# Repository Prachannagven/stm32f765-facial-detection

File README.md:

# Introduction
The goal of this project is to build a 50x50mm drone, capable of autonomous flight, and recognizing humans. The final product should be able to fly towards the target.

For current protyping, I'm looking at using an OV7670 camera, which supplies up to a 320x260 frame, based on the qvga output. However, I can go as low as the qcif resolution (176x144), although I'm not sure recognition will work well on that.

# Links to Look at
[OV7670 Interfacing][https://www.youtube.com/watch?v=aanNau1RDTA]

# Hardware Design
I use an STM32F765VIT6 due to its on board DCMI block, as well as its ART accelerator to speed up computations. It pairs with a TOF sensor, a BMP280 barometer, IMU and magnetic field sensor for full attitude determination.

Four brushed DC motors are used for this system, allowing for lightweight control. The only limitation here is how heavy the entire system is going to be. It can carry approximately 100-200 grams, which is well within our weight budget.

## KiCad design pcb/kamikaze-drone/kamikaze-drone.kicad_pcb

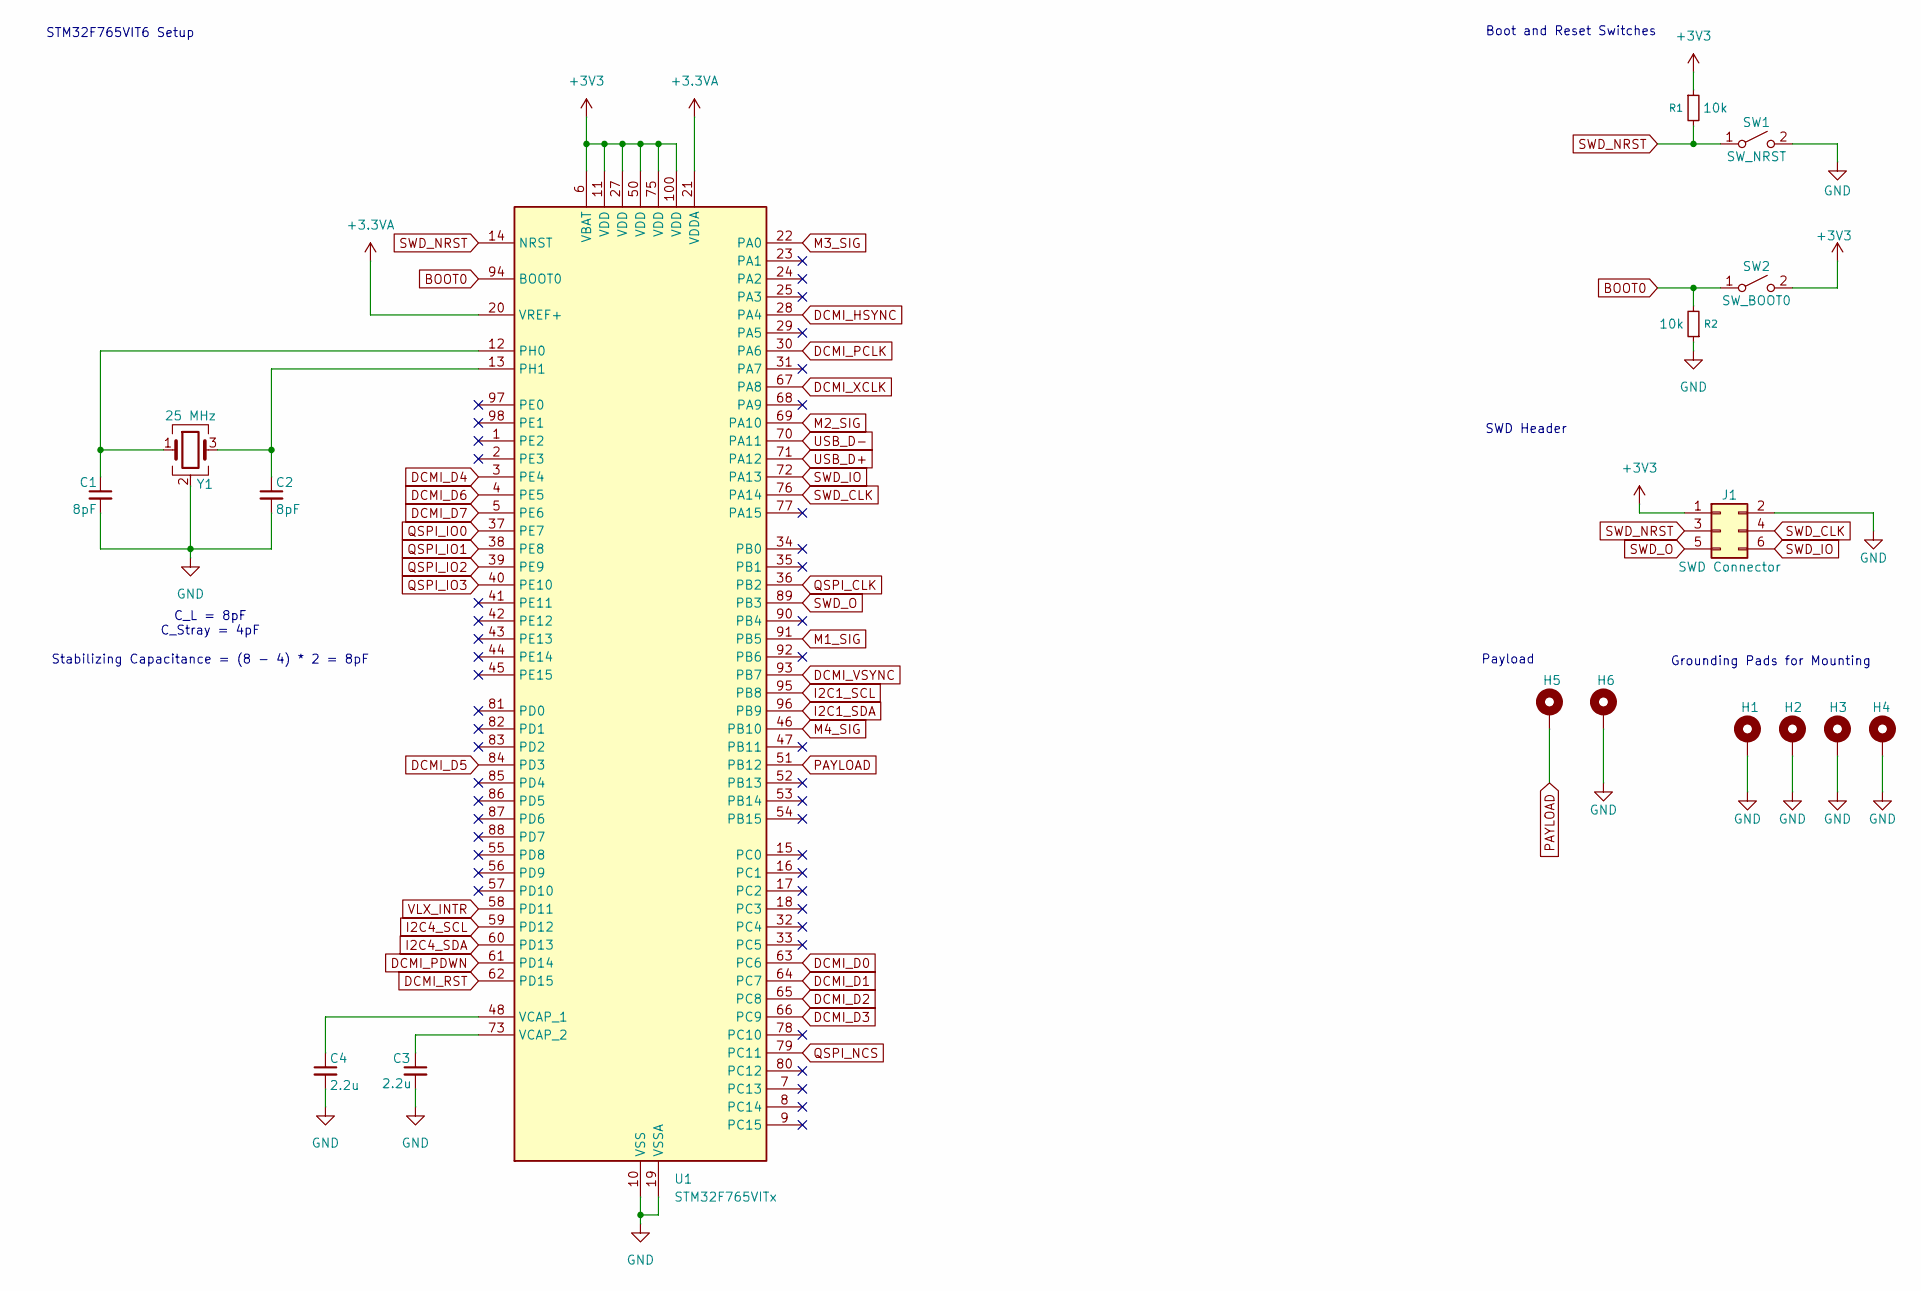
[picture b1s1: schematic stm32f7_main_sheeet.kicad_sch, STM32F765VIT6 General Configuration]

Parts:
C1, C2: 8pF; C_0603_1608Metric_Pad1.08x0.95mm_HandSolder
C3, C4: 2.2u; C_0805_2012Metric_Pad1.18x1.45mm_HandSolder
H1, H2, H3, H4: Gnd; MountingHole_2.2mm_M2_DIN965_Pad_TopBottom
H5, H6: Gnd; payload-pad
J1: SWD Connector; PinHeader_2x03_P2.54mm_Vertical_SMD
R1, R2: 10k; R_0603_1608Metric_Pad0.98x0.95mm_HandSolder
SW1: SW_NRST; button-footprint
SW2: SW_BOOT0; SW_DIP_SPSTx01_Slide_6.7x4.1mm_W6.73mm_P2.54mm_LowProfile_J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
U1: STM32F765VITx; LQFP-100_14x14mm_P0.5mm
Y1: 25 MHz; crysal-25MHz-2.55mm_x_2.05mm-2-4G

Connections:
+3.3VA: U1.20 (VREF+), U1.21 (VDDA); also elsewhere on the board
+3V3: J1.1, R1.1, SW2.2 (B), U1.6 (VBAT), U1.11 (VDD), U1.27 (VDD), U1.50 (VDD), U1.75 (VDD), U1.100 (VDD); also elsewhere on the board
BOOT0: R2.2, SW2.1 (A), U1.94 (BOOT0)
DCMI_D0: U1.63 (PC6); also elsewhere on the board
DCMI_D1: U1.64 (PC7); also elsewhere on the board
DCMI_D2: U1.65 (PC8); also elsewhere on the board
DCMI_D3: U1.66 (PC9); also elsewhere on the board
DCMI_D4: U1.3 (PE4); also elsewhere on the board
DCMI_D5: U1.84 (PD3); also elsewhere on the board
DCMI_D6: U1.4 (PE5); also elsewhere on the board
DCMI_D7: U1.5 (PE6); also elsewhere on the board
DCMI_HSYNC: U1.28 (PA4); also elsewhere on the board
DCMI_PCLK: U1.30 (PA6); also elsewhere on the board
DCMI_PDWN: U1.61 (PD14); also elsewhere on the board
DCMI_RST: U1.62 (PD15); also elsewhere on the board
DCMI_VSYNC: U1.93 (PB7); also elsewhere on the board
DCMI_XCLK: U1.67 (PA8); also elsewhere on the board
GND: C1.2, C2.2, C3.2, C4.2, H1.1, H2.1, H3.1, H4.1, H6.1, J1.2, R2.1, SW1.2 (B), U1.10 (VSS), U1.19 (VSSA), U1.26 (VSS), U1.49 (VSS), U1.74 (VSS), U1.99 (VSS), Y1.2 (G), Y1.4 (G); also elsewhere on the board
I2C1_SCL: U1.95 (PB8); also elsewhere on the board
I2C1_SDA: U1.96 (PB9); also elsewhere on the board
I2C4_SCL: U1.59 (PD12); also elsewhere on the board
I2C4_SDA: U1.60 (PD13); also elsewhere on the board
M1_SIG: U1.91 (PB5); also elsewhere on the board
M2_SIG: U1.69 (PA10); also elsewhere on the board
M3_SIG: U1.22 (PA0); also elsewhere on the board
M4_SIG: U1.46 (PB10); also elsewhere on the board
unnamed: C1.1, U1.12 (PH0), Y1.1
unnamed: C2.1, U1.13 (PH1), Y1.3
unnamed: C4.1, U1.48 (VCAP_1)
unnamed: C3.1, U1.73 (VCAP_2)
PAYLOAD: H5.1, U1.51 (PB12)
QSPI_CLK: U1.36 (PB2); also elsewhere on the board
QSPI_IO0: U1.37 (PE7); also elsewhere on the board
QSPI_IO1: U1.38 (PE8); also elsewhere on the board
QSPI_IO2: U1.39 (PE9); also elsewhere on the board
QSPI_IO3: U1.40 (PE10); also elsewhere on the board
QSPI_NCS: U1.79 (PC11); also elsewhere on the board
SWD_CLK: J1.4, U1.76 (PA14)
SWD_IO: J1.6, U1.72 (PA13)
SWD_NRST: J1.3, R1.2, SW1.1 (A), U1.14 (NRST)
SWD_O: J1.5, U1.89 (PB3)
USB_D+: U1.71 (PA12); also elsewhere on the board
USB_D-: U1.70 (PA11); also elsewhere on the board
VLX_INTR: U1.58 (PD11); also elsewhere on the board

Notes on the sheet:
Payload
Grounding Pads for Mounting
C_L = 8pF C_Stray = 4pF Stabilizing Capacitance = (8 - 4) * 2 = 8pF
Boot and Reset Switches
SWD Header
STM32F765VIT6 Setup

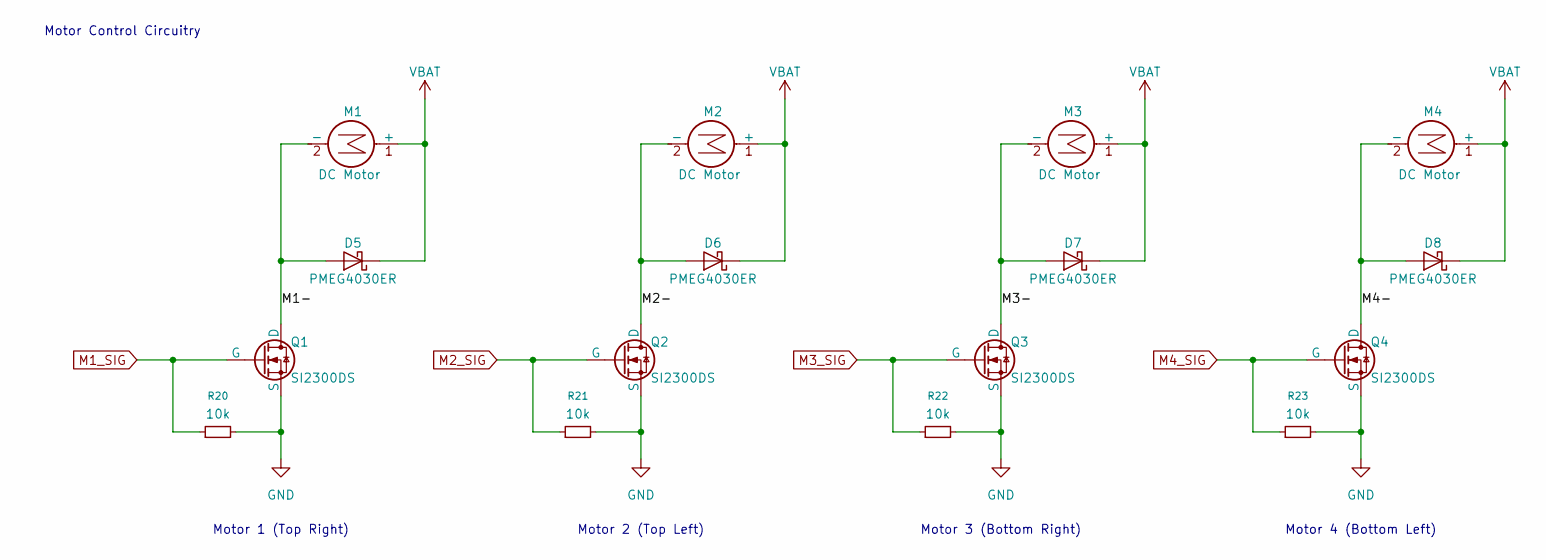
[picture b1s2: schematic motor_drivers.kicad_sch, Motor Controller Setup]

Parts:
D5, D6, D7, D8: PMEG4030ER; Nexperia_CFP3_SOD-123W
M1, M2, M3, M4: DC Motor; motor-attachment-pads
Q1, Q2, Q3, Q4: SI2300DS; SOT-23-3
R20, R21, R22, R23: 10k; R_0603_1608Metric_Pad0.98x0.95mm_HandSolder

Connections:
/Motors and Motor Drivers/M1-: D5.2 (A), M1.2 (-), Q1.3 (D)
/Motors and Motor Drivers/M2-: D6.2 (A), M2.2 (-), Q2.3 (D)
/Motors and Motor Drivers/M3-: D7.2 (A), M3.2 (-), Q3.3 (D)
/Motors and Motor Drivers/M4-: D8.2 (A), M4.2 (-), Q4.3 (D)
GND: Q1.2 (S), Q2.2 (S), Q3.2 (S), Q4.2 (S), R20.2, R21.2, R22.2, R23.2; also elsewhere on the board
M1_SIG: Q1.1 (G), R20.1; also elsewhere on the board
M2_SIG: Q2.1 (G), R21.1; also elsewhere on the board
M3_SIG: Q3.1 (G), R22.1; also elsewhere on the board
M4_SIG: Q4.1 (G), R23.1; also elsewhere on the board
VBAT: D5.1 (K), D6.1 (K), D7.1 (K), D8.1 (K), M1.1 (+), M2.1 (+), M3.1 (+), M4.1 (+); also elsewhere on the board

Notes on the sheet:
Motor 4 (Bottom Left)
Motor Control Circuitry
Motor 2 (Top Left)
Motor 1 (Top Right)
Motor 3 (Bottom Right)

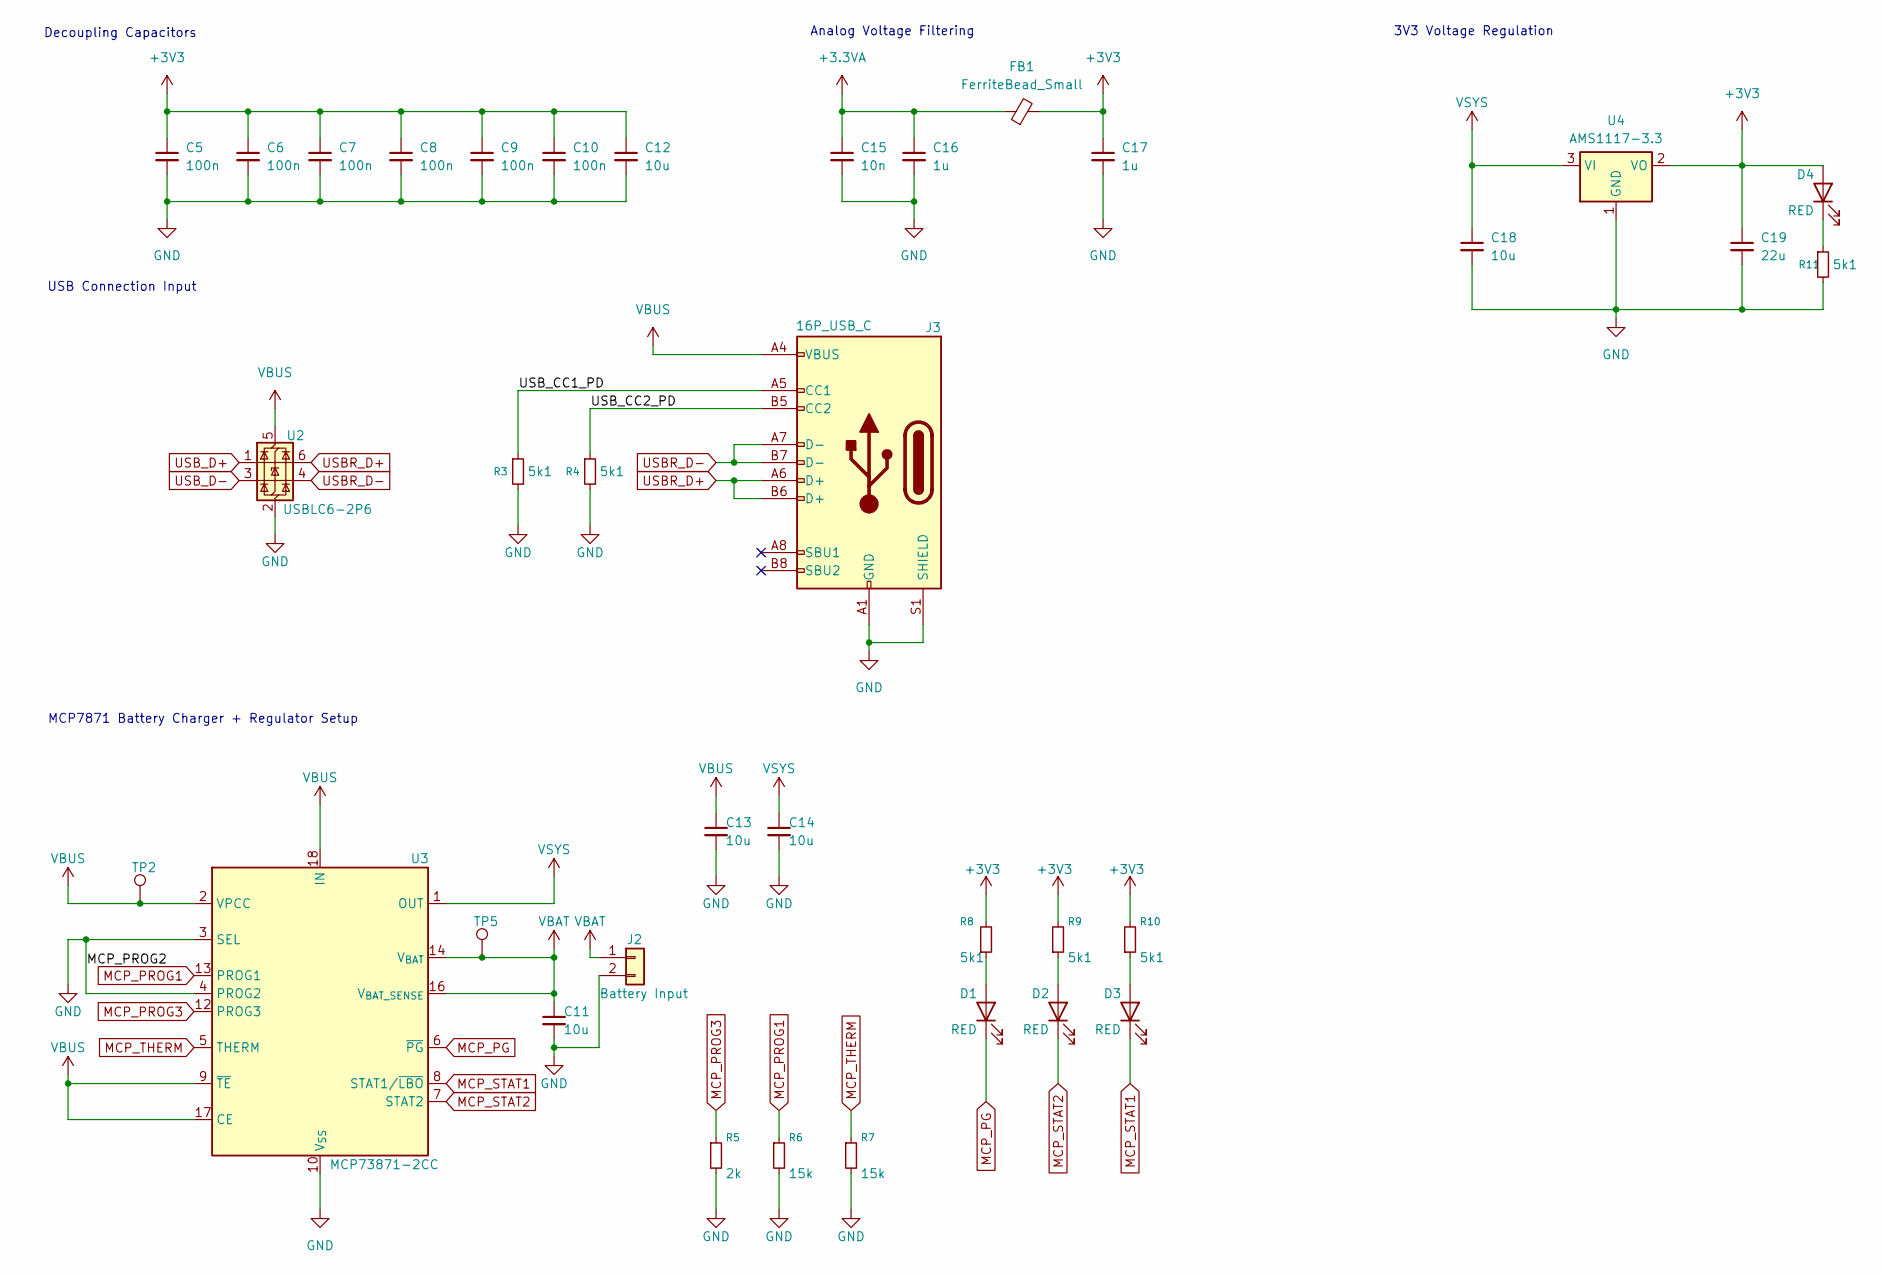
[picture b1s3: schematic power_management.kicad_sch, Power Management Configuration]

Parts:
C5, C6, C7, C8, C9, C10: 100n; C_0603_1608Metric_Pad1.08x0.95mm_HandSolder
C11, C13, C14, C18: 10u; C_0603_1608Metric_Pad1.08x0.95mm_HandSolder
C12: 10u; C_0805_2012Metric_Pad1.18x1.45mm_HandSolder
C15: 10n; C_0603_1608Metric_Pad1.08x0.95mm_HandSolder
C16, C17: 1u; C_0603_1608Metric_Pad1.08x0.95mm_HandSolder
C19: 22u; C_0603_1608Metric_Pad1.08x0.95mm_HandSolder
D1, D2, D3, D4: RED; LED_0805_2012Metric_Pad1.15x1.40mm_HandSolder
FB1: FerriteBead_Small; L_0805_2012Metric_Pad1.05x1.20mm_HandSolder
J2: Battery Input; motor-attachment-pads
J3: 16P_USB_C; USB_C_Receptacle_G-Switch_GT-USB-7010ASV
R3, R4, R8, R9, R10, R11: 5k1; R_0603_1608Metric_Pad0.98x0.95mm_HandSolder
R5: 2k; R_0603_1608Metric_Pad0.98x0.95mm_HandSolder
R6, R7: 15k; R_0603_1608Metric_Pad0.98x0.95mm_HandSolder
TP2, TP5: TestPoint; TestPoint_Pad_D1.0mm
U2: USBLC6-2P6; SOT-666
U3: MCP73871-2CC; QFN-20-1EP_4x4mm_P0.5mm_EP2.5x2.5mm
U4: AMS1117-3.3; SOT-223-3_TabPin2

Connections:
+3.3VA: C15.1, C16.1, FB1.1; also elsewhere on the board
+3V3: C5.1, C6.1, C7.1, C8.1, C9.1, C10.1, C12.1, C17.1, C19.1, D4.2 (A), FB1.2, R8.2, R9.2, R10.2, U4.2 (VO); also elsewhere on the board
/Power Management/USB_CC1_PD: J3.A5 (CC1), R3.1
/Power Management/USB_CC2_PD: J3.B5 (CC2), R4.1
GND: C5.2, C6.2, C7.2, C8.2, C9.2, C10.2, C11.2, C12.2, C13.2, C14.2, C15.2, C16.2, C17.2, C18.2, C19.2, J2.2, J3.A1 (GND), J3.A12 (GND), J3.B1 (GND), J3.B12 (GND), J3.S1 (SHIELD), R3.2, R4.2, R5.2, R6.2, R7.2, R11.2, U2.2 (GND), U3.3 (SEL), U3.4 (PROG2), U3.10 (V_{SS}), U3.11 (V_{SS}), U3.21 (V_{SS}), U4.1 (GND); also elsewhere on the board
MCP_PG: D1.1 (K), U3.6 (~PG)
MCP_PROG1: R6.1, U3.13 (PROG1)
MCP_PROG3: R5.1, U3.12 (PROG3)
MCP_STAT1: D3.1 (K), U3.8 (STAT1/~LBO)
MCP_STAT2: D2.1 (K), U3.7 (STAT2)
MCP_THERM: R7.1, U3.5 (THERM)
unnamed: D1.2 (A), R8.1
unnamed: D2.2 (A), R9.1
unnamed: D3.2 (A), R10.1
unnamed: D4.1 (K), R11.1
USBR_D+: J3.A6 (D+), J3.B6 (D+), U2.6 (I/O1)
USBR_D-: J3.A7 (D-), J3.B7 (D-), U2.4 (I/O2)
USB_D+: U2.1 (I/O1); also elsewhere on the board
USB_D-: U2.3 (I/O2); also elsewhere on the board
VBAT: C11.1, J2.1, TP5.1, U3.14 (V_{BAT}), U3.15 (V_{BAT}), U3.16 (V_{BAT_SENSE}); also elsewhere on the board
VBUS: C13.1, J3.A4 (VBUS), J3.A9 (VBUS), J3.B4 (VBUS), J3.B9 (VBUS), TP2.1, U2.5 (VBUS), U3.2 (VPCC), U3.9 (~TE), U3.17 (CE), U3.18 (IN), U3.19 (IN)
VSYS: C14.1, C18.1, U3.1 (OUT), U3.20 (OUT), U4.3 (VI)

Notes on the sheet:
MCP7871 Battery Charger + Regulator Setup
Analog Voltage Filtering
3V3 Voltage Regulation
USB Connection Input
Decoupling Capacitors

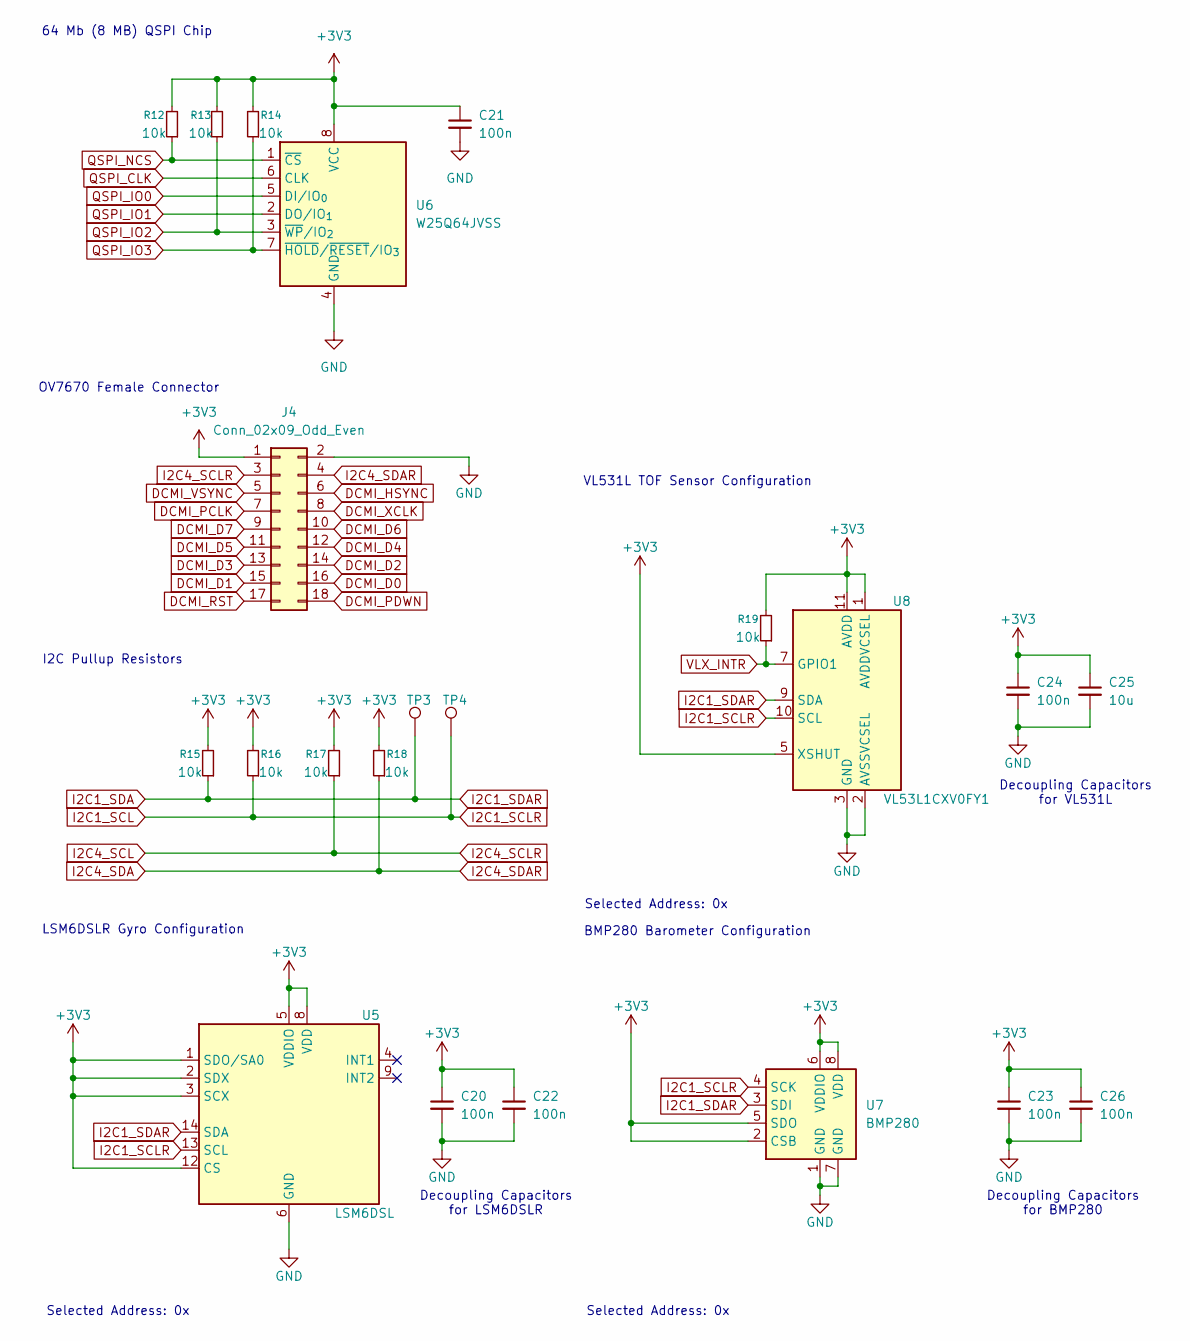
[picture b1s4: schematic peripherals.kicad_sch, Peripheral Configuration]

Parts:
C20, C21, C22, C23, C24, C26: 100n; C_0603_1608Metric_Pad1.08x0.95mm_HandSolder
C25: 10u; C_0603_1608Metric_Pad1.08x0.95mm_HandSolder
J4: Conn_02x09_Odd_Even; IDC-Header_2x09_P2.54mm_Horizontal
R12, R13, R14, R15, R16, R17, R18, R19: 10k; R_0603_1608Metric_Pad0.98x0.95mm_HandSolder
TP3, TP4: TestPoint; TestPoint_Pad_D1.0mm
U5: LSM6DSL; LGA-14_3x2.5mm_P0.5mm_LayoutBorder3x4y
U6: W25Q64JVSS; SOIC-8_5.3x5.3mm_P1.27mm
U7: BMP280; Bosch_LGA-8_2x2.5mm_P0.65mm_ClockwisePinNumbering
U8: VL53L1CXV0FY1; ST_VL53L1x

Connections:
+3V3: C20.1, C21.1, C22.1, C23.1, C24.1, C25.1, C26.1, J4.1, R12.2, R13.2, R14.2, R15.2, R16.2, R17.2, R18.2, R19.2, U5.1 (SDO/SA0), U5.2 (SDX), U5.3 (SCX), U5.5 (VDDIO), U5.8 (VDD), U5.12 (CS), U6.8 (VCC), U7.2 (CSB), U7.5 (SDO), U7.6 (VDDIO), U7.8 (VDD), U8.1 (AVDDVCSEL), U8.5 (XSHUT), U8.11 (AVDD); also elsewhere on the board
DCMI_D0: J4.16; also elsewhere on the board
DCMI_D1: J4.15; also elsewhere on the board
DCMI_D2: J4.14; also elsewhere on the board
DCMI_D3: J4.13; also elsewhere on the board
DCMI_D4: J4.12; also elsewhere on the board
DCMI_D5: J4.11; also elsewhere on the board
DCMI_D6: J4.10; also elsewhere on the board
DCMI_D7: J4.9; also elsewhere on the board
DCMI_HSYNC: J4.6; also elsewhere on the board
DCMI_PCLK: J4.7; also elsewhere on the board
DCMI_PDWN: J4.18; also elsewhere on the board
DCMI_RST: J4.17; also elsewhere on the board
DCMI_VSYNC: J4.5; also elsewhere on the board
DCMI_XCLK: J4.8; also elsewhere on the board
GND: C20.2, C21.2, C22.2, C23.2, C24.2, C25.2, C26.2, J4.2, U5.6 (GND), U5.7 (GND), U6.4 (GND), U7.1 (GND), U7.7 (GND), U8.2 (AVSSVCSEL), U8.3 (GND), U8.4 (GND), U8.6 (GND), U8.12 (GND); also elsewhere on the board
I2C1_SCL: R16.1, TP4.1, U5.13 (SCL), U7.4 (SCK), U8.10 (SCL); also elsewhere on the board
I2C1_SDA: R15.1, TP3.1, U5.14 (SDA), U7.3 (SDI), U8.9 (SDA); also elsewhere on the board
I2C4_SCL: J4.3, R17.1; also elsewhere on the board
I2C4_SDA: J4.4, R18.1; also elsewhere on the board
QSPI_CLK: U6.6 (CLK); also elsewhere on the board
QSPI_IO0: U6.5 (DI/IO_{0}); also elsewhere on the board
QSPI_IO1: U6.2 (DO/IO_{1}); also elsewhere on the board
QSPI_IO2: R13.1, U6.3 (~WP/IO_{2}); also elsewhere on the board
QSPI_IO3: R14.1, U6.7 (~HOLD/~RESET/IO_{3}); also elsewhere on the board
QSPI_NCS: R12.1, U6.1 (~CS); also elsewhere on the board
VLX_INTR: R19.1, U8.7 (GPIO1); also elsewhere on the board

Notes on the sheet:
I2C Pullup Resistors
Decoupling Capacitors for VL531L
64 Mb (8 MB) QSPI Chip
LSM6DSLR Gyro Configuration
Selected Address: 0x
Decoupling Capacitors for BMP280
VL531L TOF Sensor Configuration
Decoupling Capacitors for LSM6DSLR
BMP280 Barometer Configuration
OV7670 Female Connector

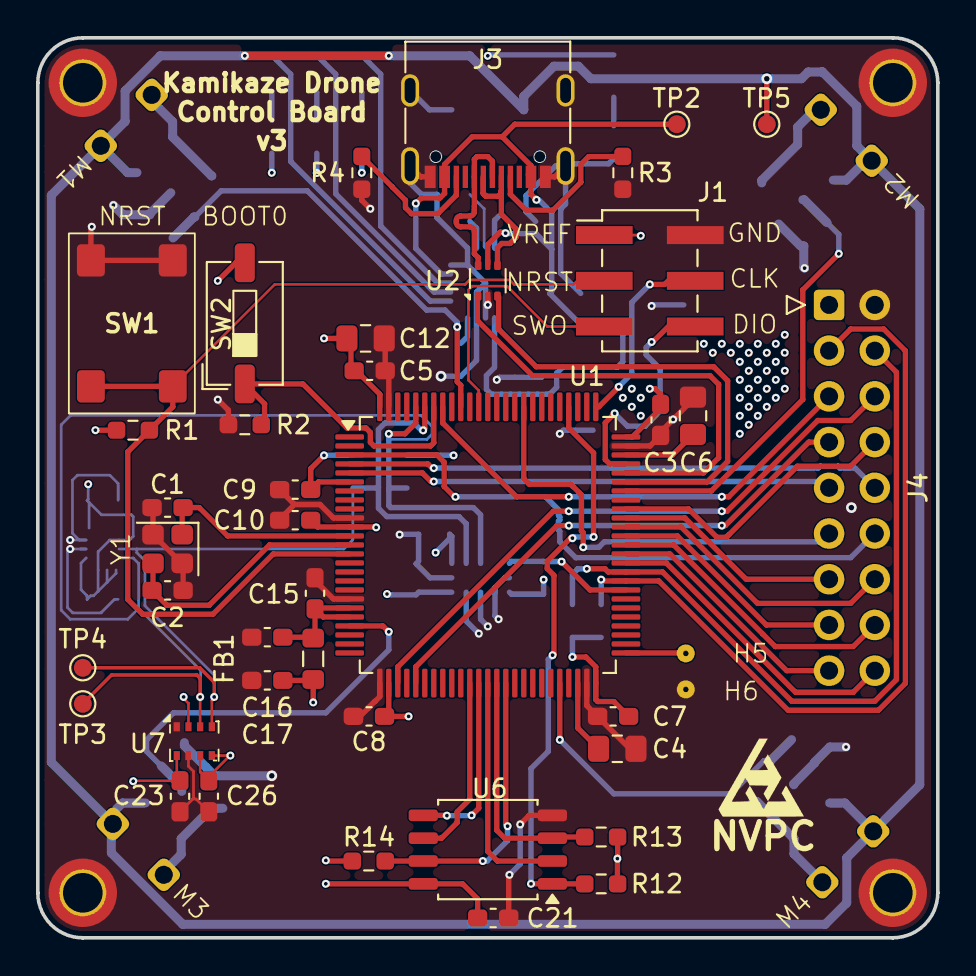
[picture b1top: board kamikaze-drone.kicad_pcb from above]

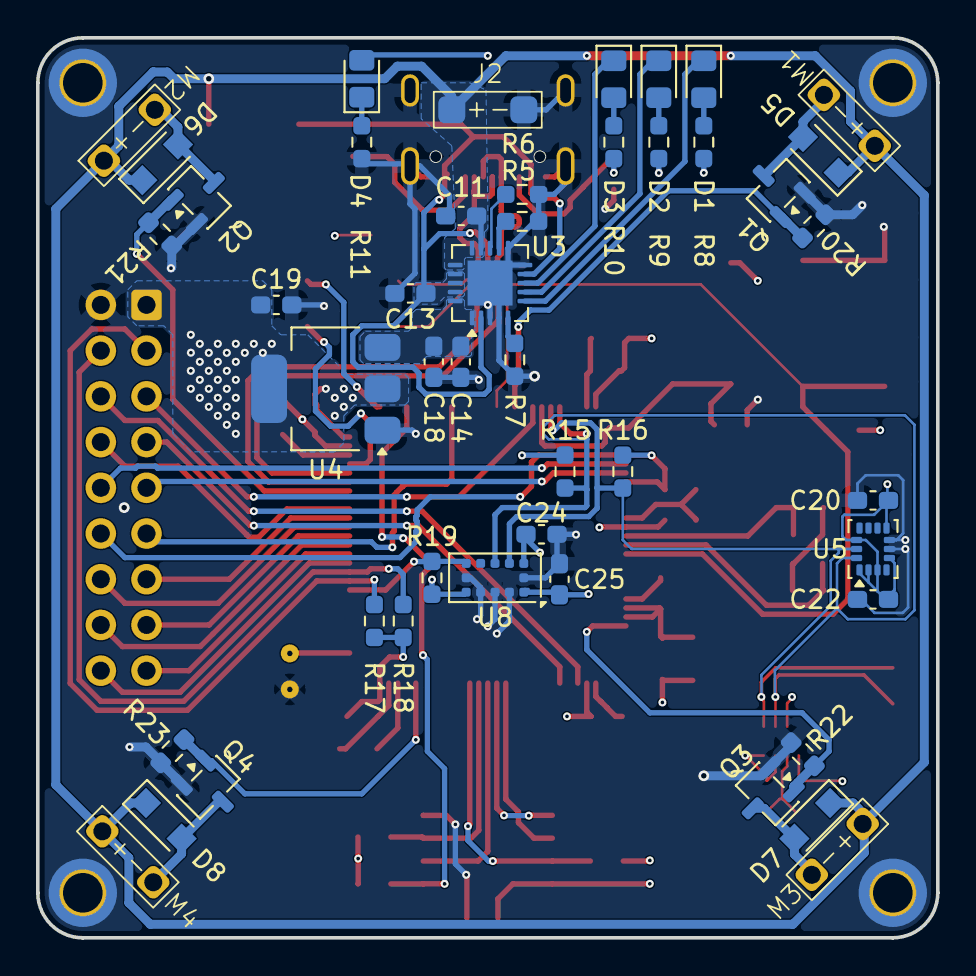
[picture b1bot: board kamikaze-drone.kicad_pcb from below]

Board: 4 copper layers, 50.0 x 50.0 mm, 92 parts (46 on the bottom side), 65 nets.

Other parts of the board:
NVPC: LOGO; logo

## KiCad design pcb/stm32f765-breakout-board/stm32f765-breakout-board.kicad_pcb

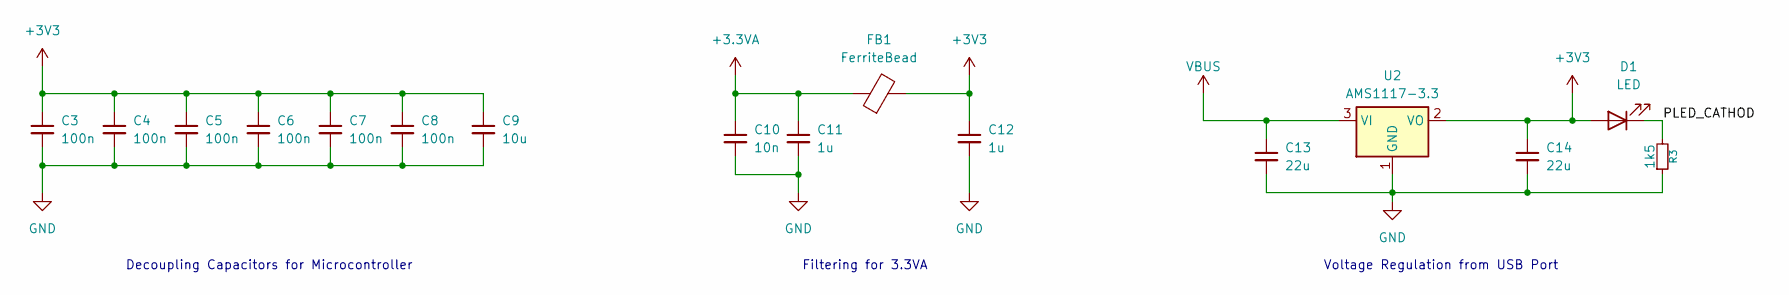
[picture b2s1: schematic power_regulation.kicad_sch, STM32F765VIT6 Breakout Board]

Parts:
C3, C4, C5, C6, C7, C8: 100n; C_0805_2012Metric_Pad1.18x1.45mm_HandSolder
C9: 10u; C_0805_2012Metric_Pad1.18x1.45mm_HandSolder
C10: 10n; C_0805_2012Metric_Pad1.18x1.45mm_HandSolder
C11, C12: 1u; C_0805_2012Metric_Pad1.18x1.45mm_HandSolder
C13, C14: 22u; C_0805_2012Metric_Pad1.18x1.45mm_HandSolder
D1: LED; LED_0805_2012Metric_Pad1.15x1.40mm_HandSolder
FB1: FerriteBead; L_0805_2012Metric_Pad1.05x1.20mm_HandSolder
R3: 1k5; R_0805_2012Metric_Pad1.20x1.40mm_HandSolder
U2: AMS1117-3.3; SOT-223-3_TabPin2

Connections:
+3.3VA: C10.1, C11.1, FB1.1; also elsewhere on the board
+3V3: C3.1, C4.1, C5.1, C6.1, C7.1, C8.1, C9.1, C12.1, C14.1, D1.2 (A), FB1.2, U2.2 (VO); also elsewhere on the board
/Power Regulation/PLED_CATHOD: D1.1 (K), R3.2
GND: C3.2, C4.2, C5.2, C6.2, C7.2, C8.2, C9.2, C10.2, C11.2, C12.2, C13.2, C14.2, R3.1, U2.1 (GND); also elsewhere on the board
VBUS: C13.1, U2.3 (VI); also elsewhere on the board

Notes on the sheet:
Filtering for 3.3VA
Voltage Regulation from USB Port
Decoupling Capacitors for Microcontroller

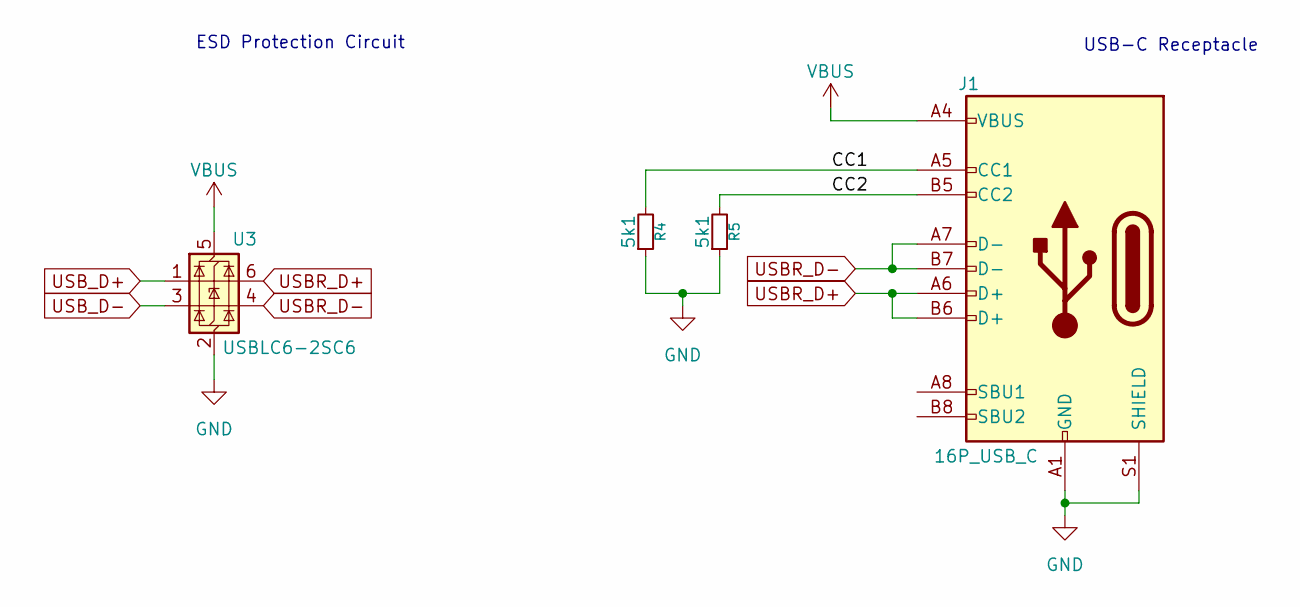
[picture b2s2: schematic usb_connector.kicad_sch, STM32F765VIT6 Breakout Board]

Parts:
J1: 16P_USB_C; USB_C_Receptacle_G-Switch_GT-USB-7010ASV
R4, R5: 5k1; R_0805_2012Metric_Pad1.20x1.40mm_HandSolder
U3: USBLC6-2SC6; SOT-23-6

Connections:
/USB Connector/CC1: J1.A5 (CC1), R4.2
/USB Connector/CC2: J1.B5 (CC2), R5.2
GND: J1.A1 (GND), J1.A12 (GND), J1.B1 (GND), J1.B12 (GND), J1.S1 (SHIELD), R4.1, R5.1, U3.2 (GND); also elsewhere on the board
USBR_D+: J1.A6 (D+), J1.B6 (D+), U3.6 (I/O1)
USBR_D-: J1.A7 (D-), J1.B7 (D-), U3.4 (I/O2)
USB_D+: U3.1 (I/O1); also elsewhere on the board
USB_D-: U3.3 (I/O2); also elsewhere on the board
VBUS: J1.A4 (VBUS), J1.A9 (VBUS), J1.B4 (VBUS), J1.B9 (VBUS), U3.5 (VBUS); also elsewhere on the board

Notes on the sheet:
USB-C Receptacle
ESD Protection Circuit

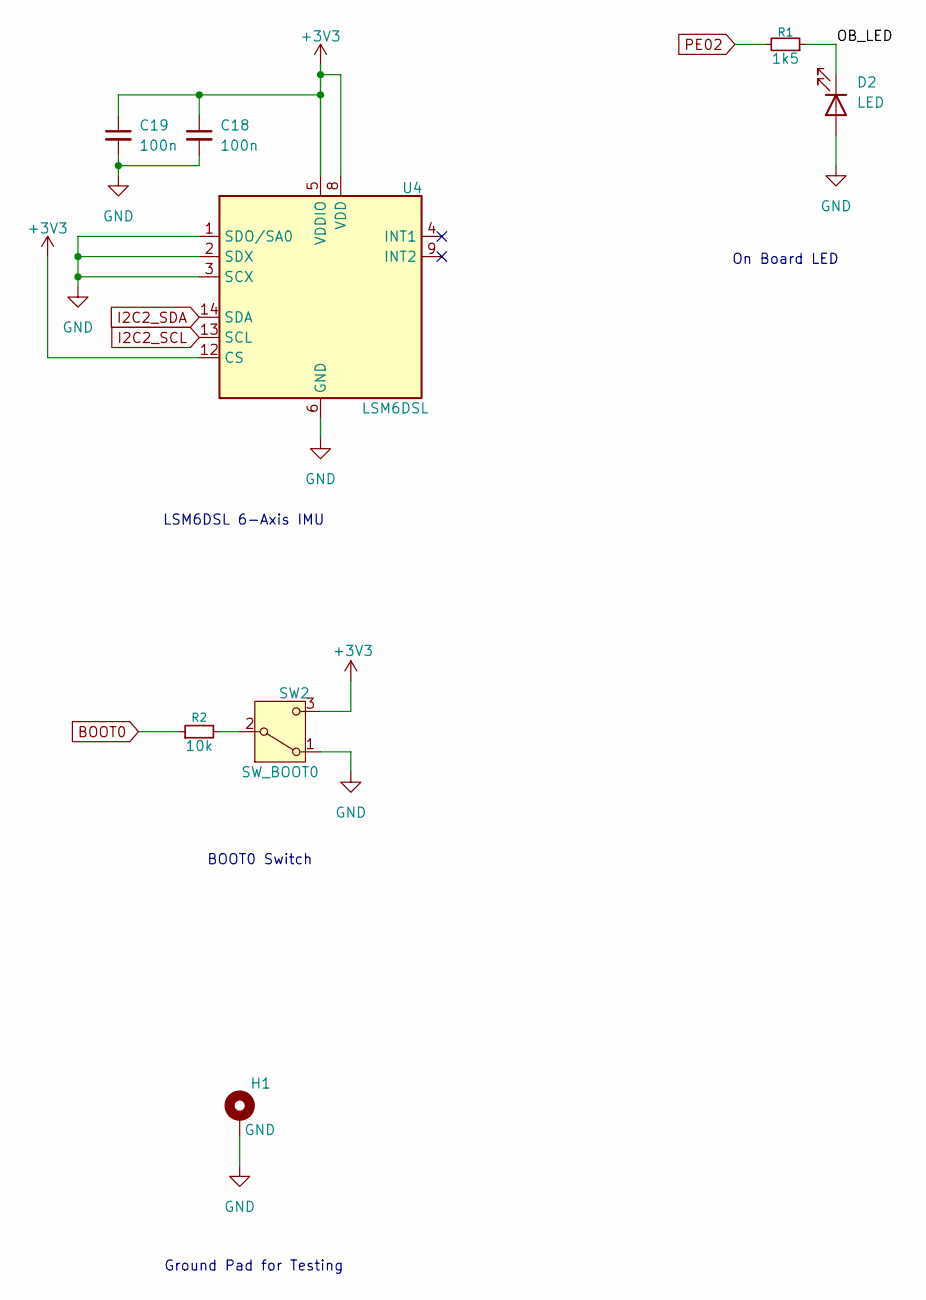
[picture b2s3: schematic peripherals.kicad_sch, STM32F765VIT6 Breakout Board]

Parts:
C18, C19: 100n; C_0805_2012Metric_Pad1.18x1.45mm_HandSolder
D2: LED; LED_0805_2012Metric_Pad1.15x1.40mm_HandSolder
H1: GND; MountingHole_2.2mm_M2_Pad
R1: 1k5; R_0805_2012Metric_Pad1.20x1.40mm_HandSolder
R2: 10k; R_0805_2012Metric_Pad1.20x1.40mm_HandSolder
SW2: SW_BOOT0; new_4.5x4.5_mm_tactile_button_1883759
U4: LSM6DSL; LGA-14_3x2.5mm_P0.5mm_LayoutBorder3x4y

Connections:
+3V3: C18.1, C19.1, SW2.3 (C), U4.5 (VDDIO), U4.8 (VDD), U4.12 (CS); also elsewhere on the board
/Peripherals/OB_LED: D2.1 (K), R1.1
BOOT0: R2.1; also elsewhere on the board
GND: C18.2, C19.2, D2.2 (A), H1.1, SW2.1 (A), U4.1 (SDO/SA0), U4.2 (SDX), U4.3 (SCX), U4.6 (GND), U4.7 (GND); also elsewhere on the board
I2C2_SCL: U4.13 (SCL); also elsewhere on the board
I2C2_SDA: U4.14 (SDA); also elsewhere on the board
unnamed: R2.2, SW2.2 (B)
PE02: R1.2; also elsewhere on the board

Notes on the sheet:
LSM6DSL 6-Axis IMU
Ground Pad for Testing
On Board LED
BOOT0 Switch

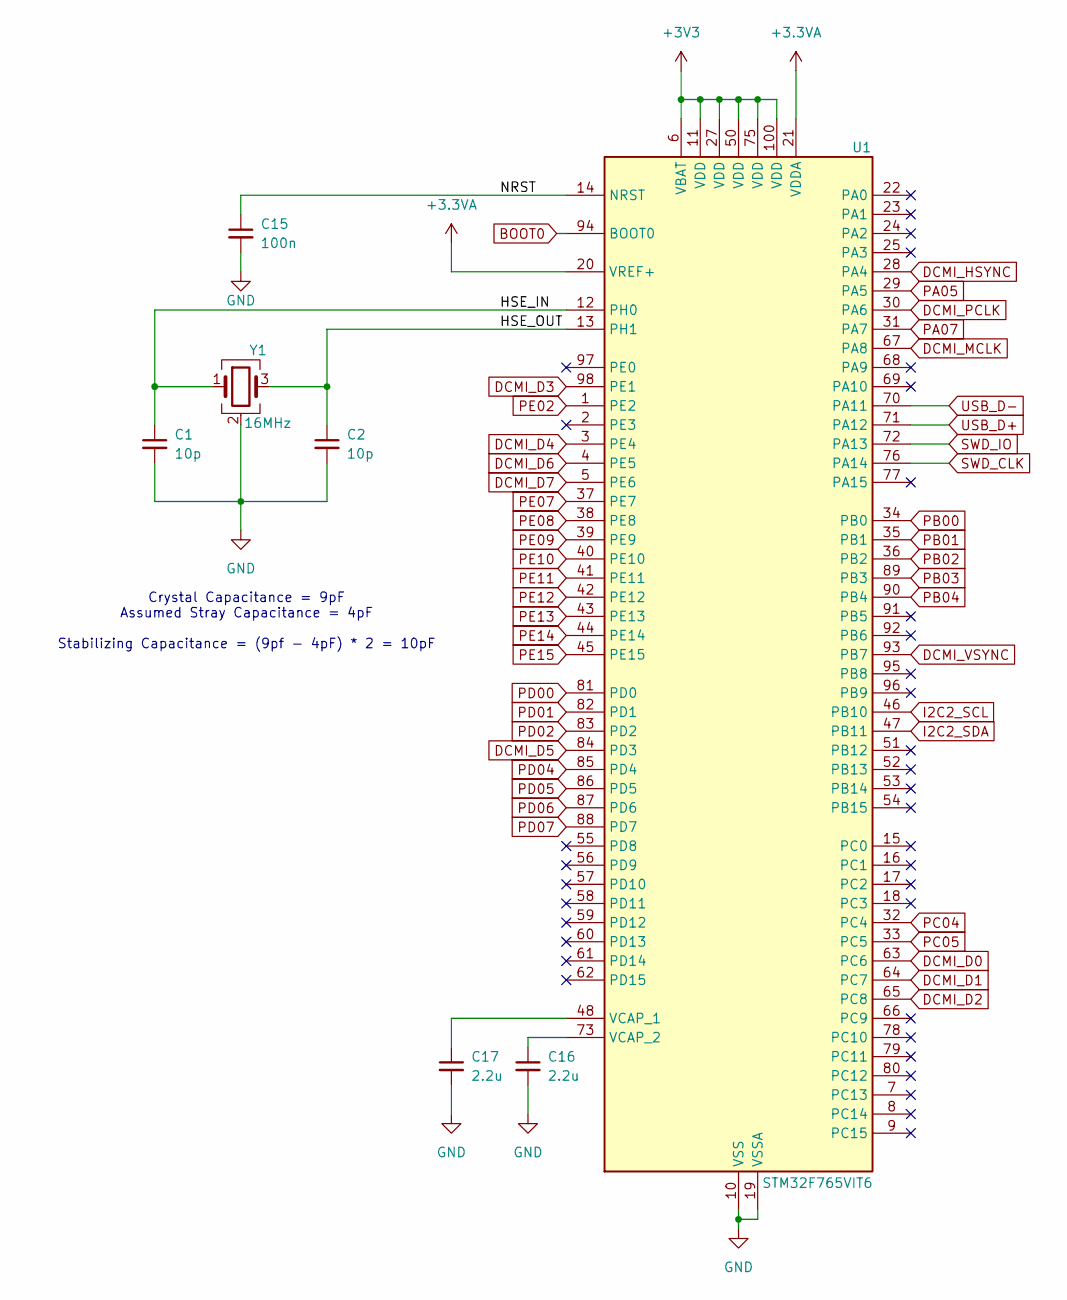
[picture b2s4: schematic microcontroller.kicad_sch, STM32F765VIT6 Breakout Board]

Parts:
C1, C2: 10p; C_0805_2012Metric_Pad1.18x1.45mm_HandSolder
C15: 100n; C_0805_2012Metric_Pad1.18x1.45mm_HandSolder
C16, C17: 2.2u; C_0805_2012Metric_Pad1.18x1.45mm_HandSolder
U1: STM32F765VIT6; LQFP-100_14x14mm_P0.5mm
Y1: 16MHz; Crystal_SMD_3225-4Pin_3.2x2.5mm_HandSoldering

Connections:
+3.3VA: U1.20 (VREF+), U1.21 (VDDA); also elsewhere on the board
+3V3: U1.6 (VBAT), U1.11 (VDD), U1.27 (VDD), U1.50 (VDD), U1.75 (VDD), U1.100 (VDD); also elsewhere on the board
/Microcontroller/HSE_IN: C1.1, U1.12 (PH0), Y1.1
/Microcontroller/HSE_OUT: C2.1, U1.13 (PH1), Y1.3
/Microcontroller/NRST: C15.1, U1.14 (NRST)
BOOT0: U1.94 (BOOT0); also elsewhere on the board
DCMI_D0: U1.63 (PC6); also elsewhere on the board
DCMI_D1: U1.64 (PC7); also elsewhere on the board
DCMI_D2: U1.65 (PC8); also elsewhere on the board
DCMI_D3: U1.98 (PE1); also elsewhere on the board
DCMI_D4: U1.3 (PE4); also elsewhere on the board
DCMI_D5: U1.84 (PD3); also elsewhere on the board
DCMI_D6: U1.4 (PE5); also elsewhere on the board
DCMI_D7: U1.5 (PE6); also elsewhere on the board
DCMI_HSYNC: U1.28 (PA4); also elsewhere on the board
DCMI_MCLK: U1.67 (PA8); also elsewhere on the board
DCMI_PCLK: U1.30 (PA6); also elsewhere on the board
DCMI_VSYNC: U1.93 (PB7); also elsewhere on the board
GND: C1.2, C2.2, C15.2, C16.2, C17.2, U1.10 (VSS), U1.19 (VSSA), U1.26 (VSS), U1.49 (VSS), U1.74 (VSS), U1.99 (VSS), Y1.2 (G), Y1.4 (G); also elsewhere on the board
I2C2_SCL: U1.46 (PB10); also elsewhere on the board
I2C2_SDA: U1.47 (PB11); also elsewhere on the board
unnamed: C17.1, U1.48 (VCAP_1)
unnamed: C16.1, U1.73 (VCAP_2)
PA05: U1.29 (PA5); also elsewhere on the board
PA07: U1.31 (PA7); also elsewhere on the board
PB00: U1.34 (PB0); also elsewhere on the board
PB01: U1.35 (PB1); also elsewhere on the board
PB02: U1.36 (PB2); also elsewhere on the board
PB03: U1.89 (PB3); also elsewhere on the board
PB04: U1.90 (PB4); also elsewhere on the board
PC04: U1.32 (PC4); also elsewhere on the board
PC05: U1.33 (PC5); also elsewhere on the board
PD00: U1.81 (PD0); also elsewhere on the board
PD01: U1.82 (PD1); also elsewhere on the board
PD02: U1.83 (PD2); also elsewhere on the board
PD04: U1.85 (PD4); also elsewhere on the board
PD05: U1.86 (PD5); also elsewhere on the board
PD06: U1.87 (PD6); also elsewhere on the board
PD07: U1.88 (PD7); also elsewhere on the board
PE02: U1.1 (PE2); also elsewhere on the board
PE07: U1.37 (PE7); also elsewhere on the board
PE08: U1.38 (PE8); also elsewhere on the board
PE09: U1.39 (PE9); also elsewhere on the board
PE10: U1.40 (PE10); also elsewhere on the board
PE11: U1.41 (PE11); also elsewhere on the board
PE12: U1.42 (PE12); also elsewhere on the board
PE13: U1.43 (PE13); also elsewhere on the board
PE14: U1.44 (PE14); also elsewhere on the board
PE15: U1.45 (PE15)
SWD_CLK: U1.76 (PA14); also elsewhere on the board
SWD_IO: U1.72 (PA13); also elsewhere on the board
USB_D+: U1.71 (PA12); also elsewhere on the board
USB_D-: U1.70 (PA11); also elsewhere on the board

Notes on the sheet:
Crystal Capacitance = 9pF Assumed Stray Capacitance = 4pF Stabilizing Capacitance = (9pf - 4pF) * 2 = 10pF
